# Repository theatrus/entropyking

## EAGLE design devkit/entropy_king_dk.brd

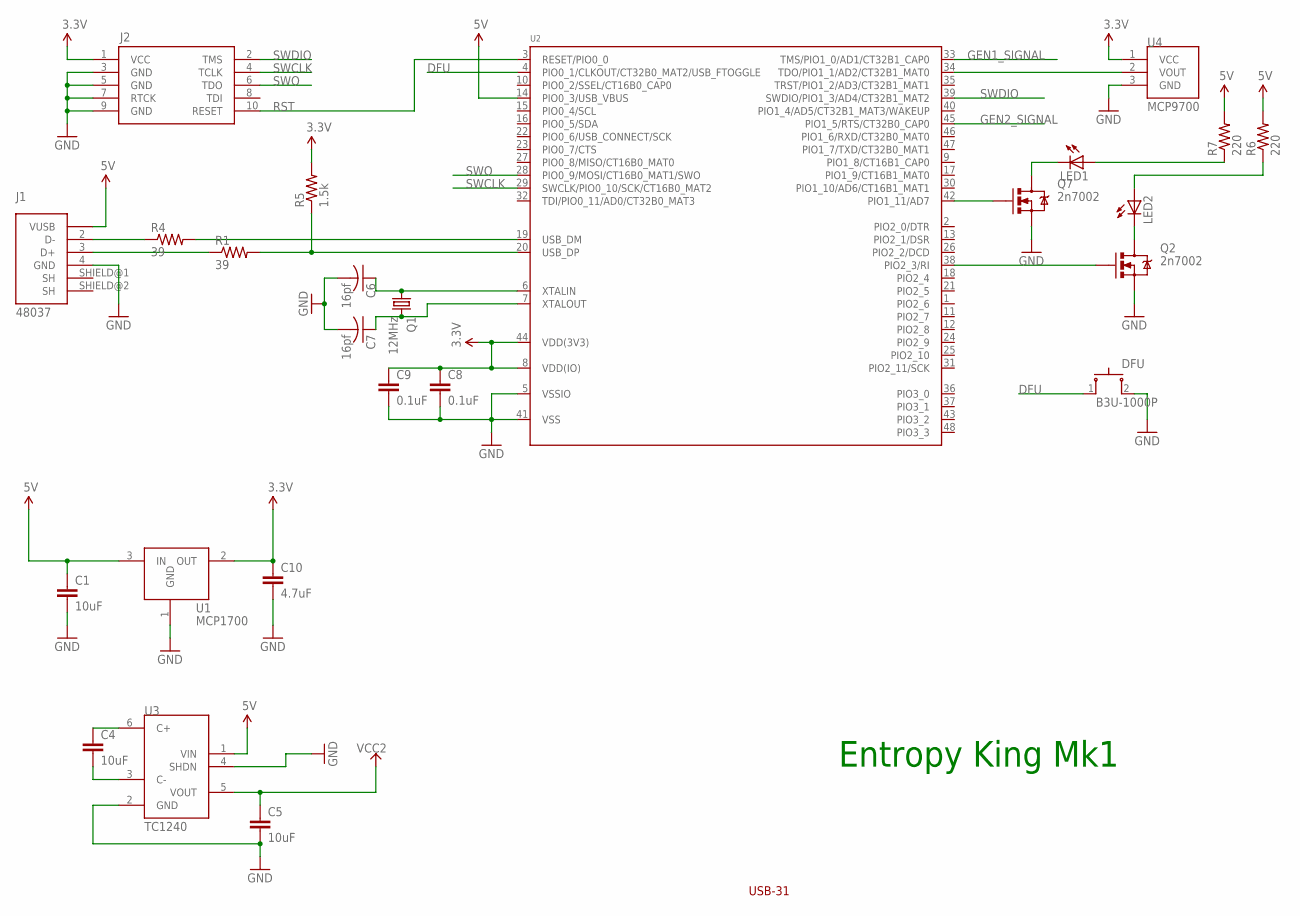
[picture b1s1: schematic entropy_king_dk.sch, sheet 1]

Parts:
C1, C4, C5: 10uF; C0805
C6, C7: 16pf; C0603
C8, C9: 0.1uF; C0603
C10: 4.7uF; C0603
CASE1: USB-31
DFU: B3U-1000P
J1: 48037
J2: ARM_MINI_10PIN_JTAG; 2X05_SMD
LED1, LED2: LED1206; LED-1206
Q1: 12MHz; CRYSTAL-SMD-5X3.2
Q2, Q7: 2n7002; SOT23-3
R1, R4: 39; R0603
R5: 1.5k; R0603
R6, R7: 220; R0603
U1: MCP1700; SOT23
U2: LPC1343_QFP; LQFP48
U3: TC1240; SOT23-6L
U4: MCP9700; SOT23

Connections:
3.3V: C8.1, C9.1, C10.1, J2.1 (VCC), R5.2, U1.2 (OUT), U2.8 (VDD(IO)), U2.44 (VDD(3V3)), U4.1 (VCC); also elsewhere on the board
5V: C1.1, J1.1 (VUSB), R6.2, R7.2, U1.3 (IN), U2.14 (PIO0_3/USB_VBUS), U3.1 (VIN)
DFU: DFU.1, U2.4 (PIO0_1/CLKOUT/CT32B0_MAT2/USB_FTOGGLE)
GEN1_SIGNAL: U2.33 (TMS/PIO1_0/AD1/CT32B1_CAP0); also elsewhere on the board
GEN2_SIGNAL: U2.45 (PIO1_5/RTS/CT32B0_CAP0); also elsewhere on the board
GND: C1.2, C5.2, C6.2, C7.2, C8.2, C9.2, C10.2, DFU.2, J1.4 (GND), J2.3 (GND), J2.5 (GND), J2.7 (RTCK), J2.9 (GND), Q2.2 (S), Q7.2 (S), U1.1 (GND), U2.5 (VSSIO), U2.41 (VSS), U3.2 (GND), U3.4 (SHDN), U4.3 (GND); also elsewhere on the board
unnamed: J1.2 (D-), R4.1
unnamed: C4.1, U3.6 (C+)
unnamed: C4.2, U3.3 (C-)
unnamed: J1.3 (D+), R1.1
unnamed: Q7.1 (G), U2.42 (PIO1_11/AD7)
unnamed: R4.2, U2.19 (USB_DM)
unnamed: R1.2, R5.1, U2.20 (USB_DP)
unnamed: Q2.1 (G), U2.38 (PIO2_3/RI)
unnamed: LED2.C, Q2.3 (D)
unnamed: LED1.C, Q7.3 (D)
unnamed: LED2.A, R6.1
unnamed: LED1.A, R7.1
unnamed: U2.34 (TDO/PIO1_1/AD2/CT32B1_MAT0), U4.2 (VOUT)
RST: J2.10 (RESET), U2.3 (RESET/PIO0_0)
SWCLK: J2.4 (TCLK), U2.29 (SWCLK/PIO0_10/SCK/CT16B0_MAT2)
SWDIO: J2.2 (TMS), U2.39 (SWDIO/PIO1_3/AD4/CT32B1_MAT2)
SWO: J2.6 (TDO), U2.28 (PIO0_9/MOSI/CT16B0_MAT1/SWO)
VCC2: C5.1, U3.5 (VOUT); also elsewhere on the board
XIN: C6.1, Q1.1, U2.6 (XTALIN)
XOUT: C7.1, Q1.3 (2), U2.7 (XTALOUT)

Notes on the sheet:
Entropy King Mk1

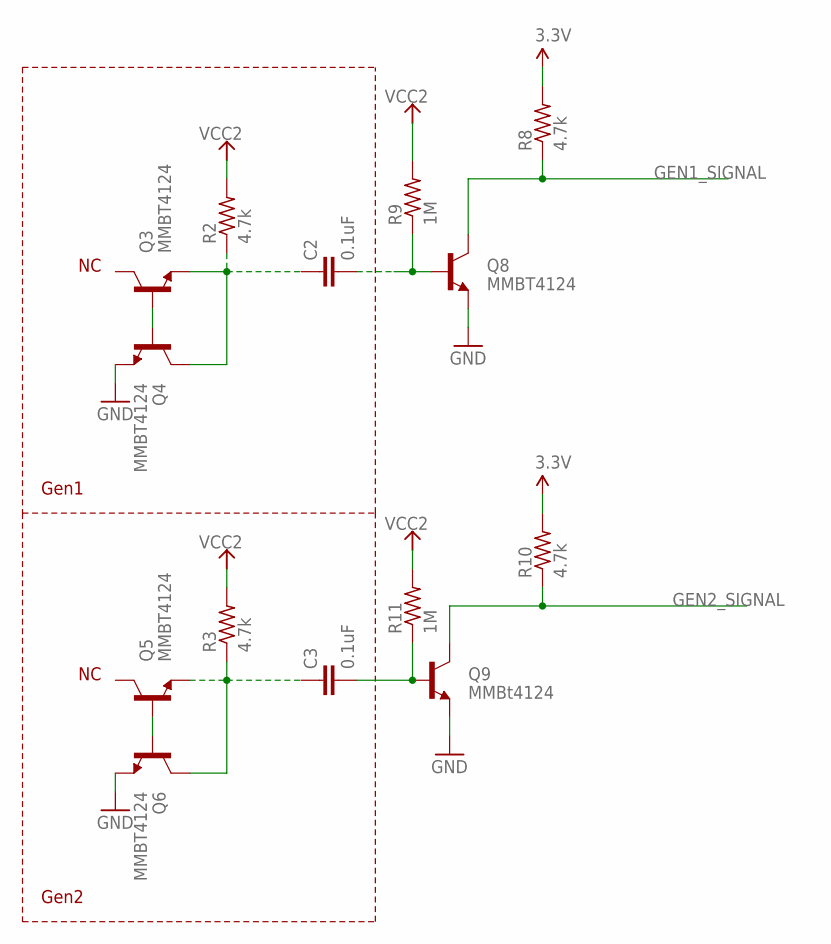
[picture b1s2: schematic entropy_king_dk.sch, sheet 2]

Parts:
C2, C3: 0.1uF; C0603
Q3, Q4, Q5, Q6, Q8: MMBT4124; SOT23-3
Q9: MMBt4124; SOT23-3
R2, R3, R8, R10: 4.7k; R0603
R9, R11: 1M; R0603

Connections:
3.3V: R8.2, R10.2; also elsewhere on the board
GEN1_SIGNAL: Q8.3 (C), R8.1; also elsewhere on the board
GEN2_SIGNAL: Q9.3 (C), R10.1; also elsewhere on the board
GND: Q4.2 (E), Q6.2 (E), Q8.2 (E), Q9.2 (E); also elsewhere on the board
unnamed: C2.2, Q8.1 (B), R9.1
unnamed: C3.2, Q9.1 (B), R11.1
unnamed: C2.1, Q3.2 (E), Q4.3 (C), R2.1
unnamed: Q3.1 (B), Q4.1 (B)
unnamed: Q5.1 (B), Q6.1 (B)
unnamed: C3.1, Q5.2 (E), Q6.3 (C), R3.1
VCC2: R2.2, R3.2, R9.2, R11.2; also elsewhere on the board

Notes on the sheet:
Gen1
Gen2

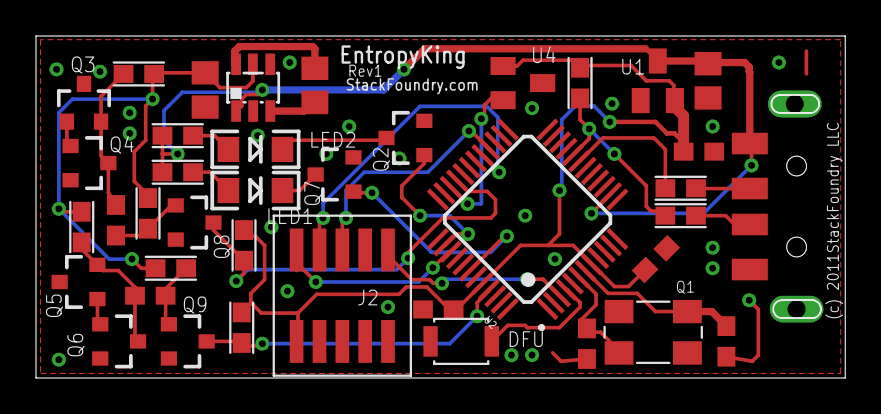
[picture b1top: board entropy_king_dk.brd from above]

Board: 2 copper layers, 44.9 x 18.9 mm, 40 parts (0 on the bottom side), 32 nets.

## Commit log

2009-08-12 Entropy king project
2009-08-25 eagle
2009-08-26 Research
2009-08-28 NEw datasheets
2009-09-17 Datasheets
2010-05-04 Adjust board
2014-04-11 Rearrange files
2014-04-11 License file

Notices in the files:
devkit/entropy_king_dk.brd:
(c) 2011StackFoundry LLC
